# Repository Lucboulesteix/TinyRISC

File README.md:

# TinyRISC
 TINYRISC is a project to design and build an 8-bit computer using discrete logic components
 See "descriptive document.docx" for technical information

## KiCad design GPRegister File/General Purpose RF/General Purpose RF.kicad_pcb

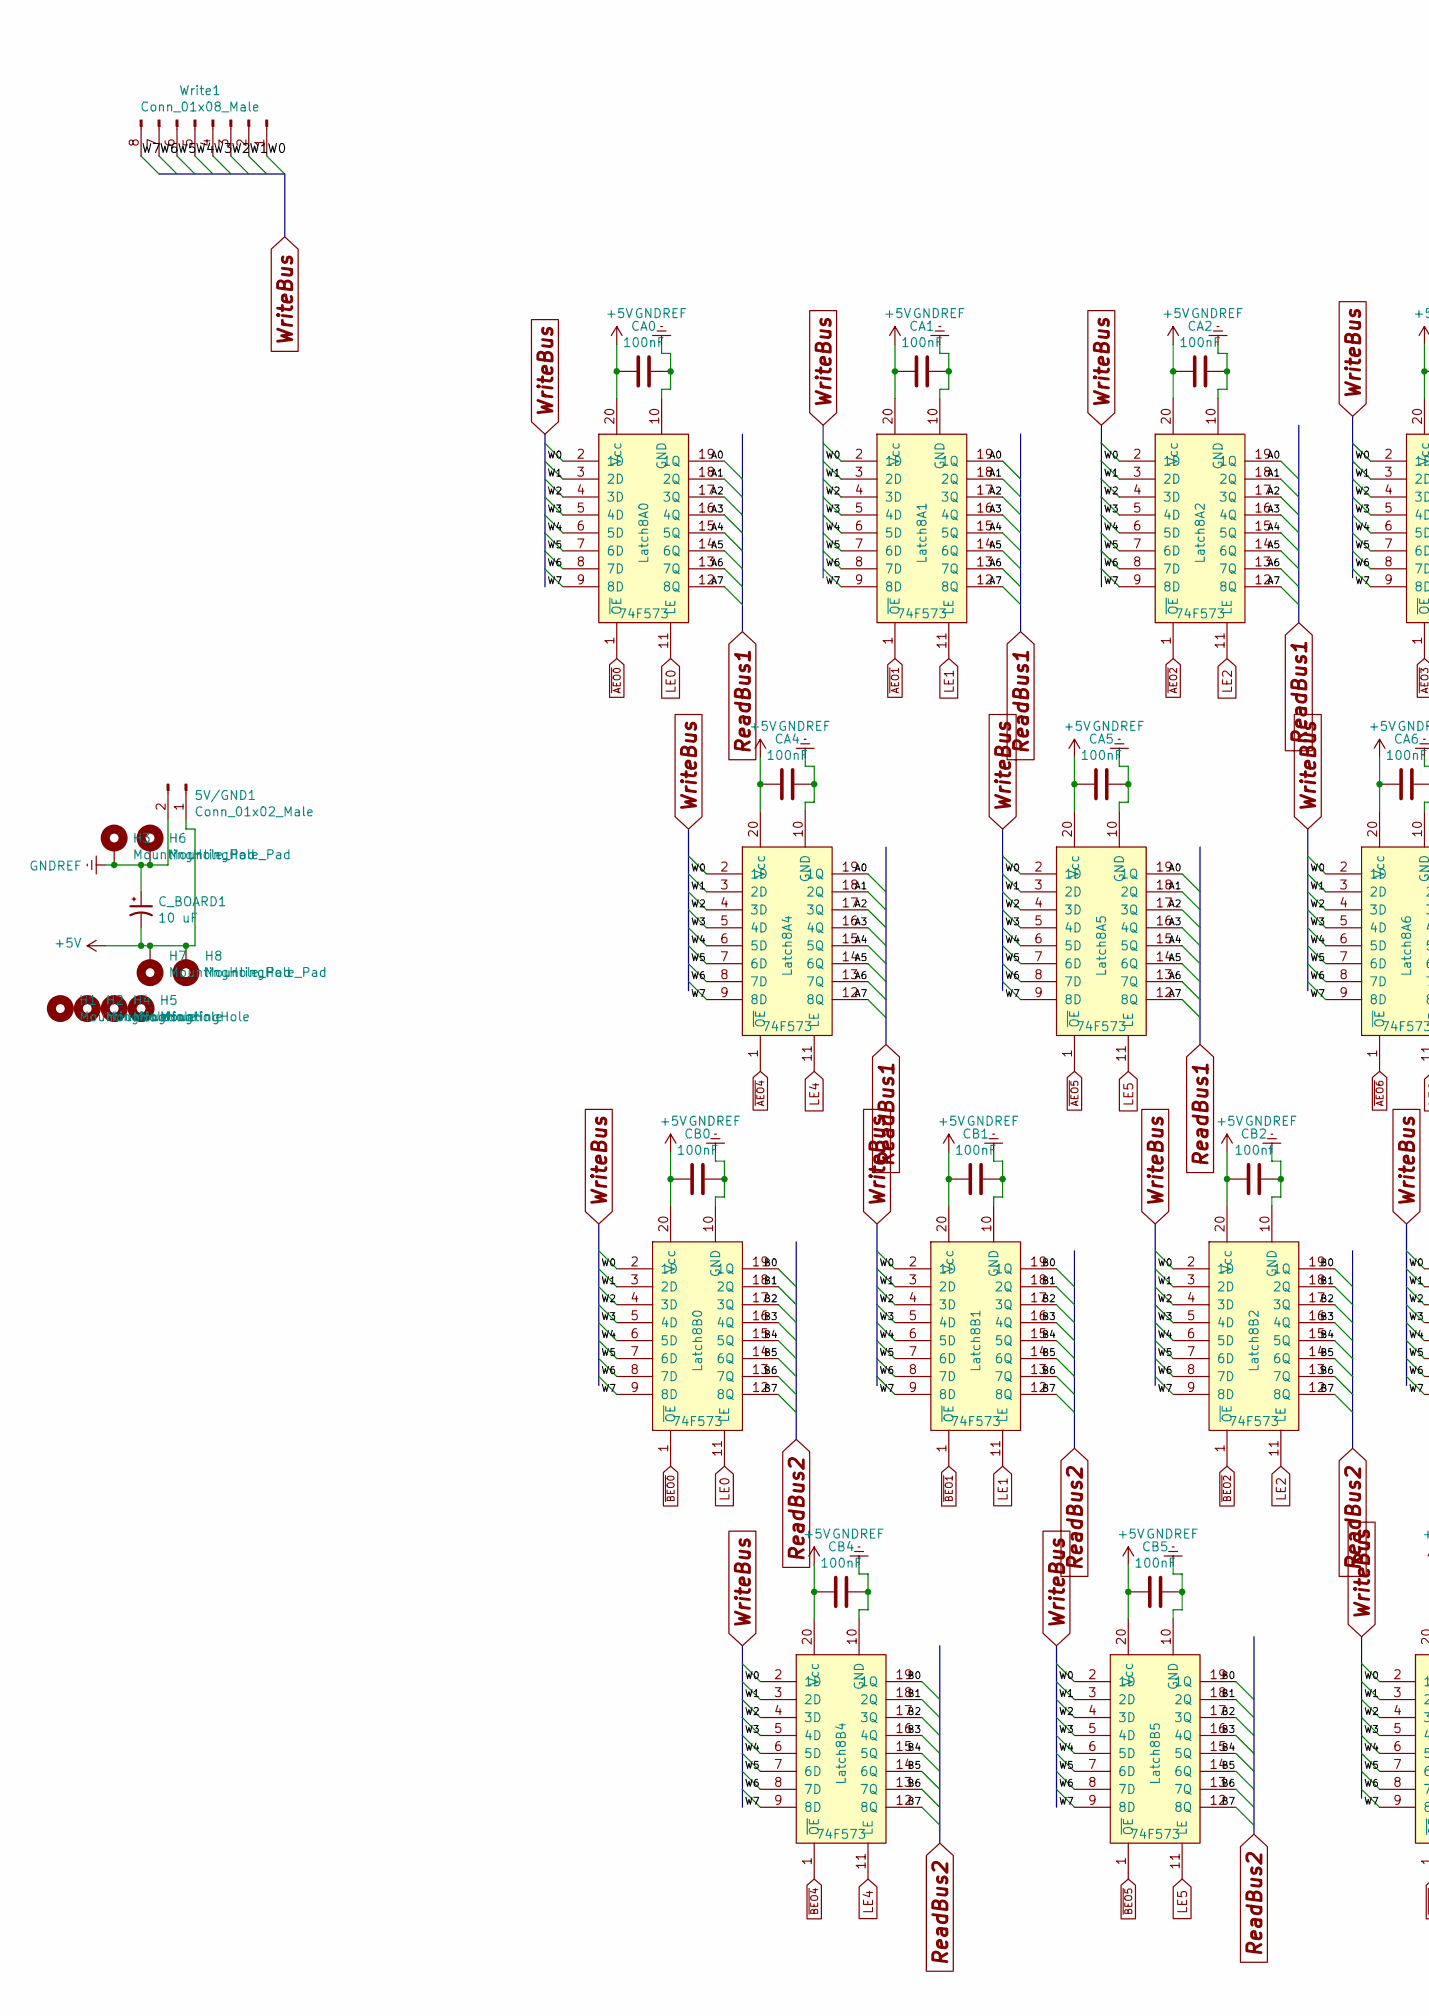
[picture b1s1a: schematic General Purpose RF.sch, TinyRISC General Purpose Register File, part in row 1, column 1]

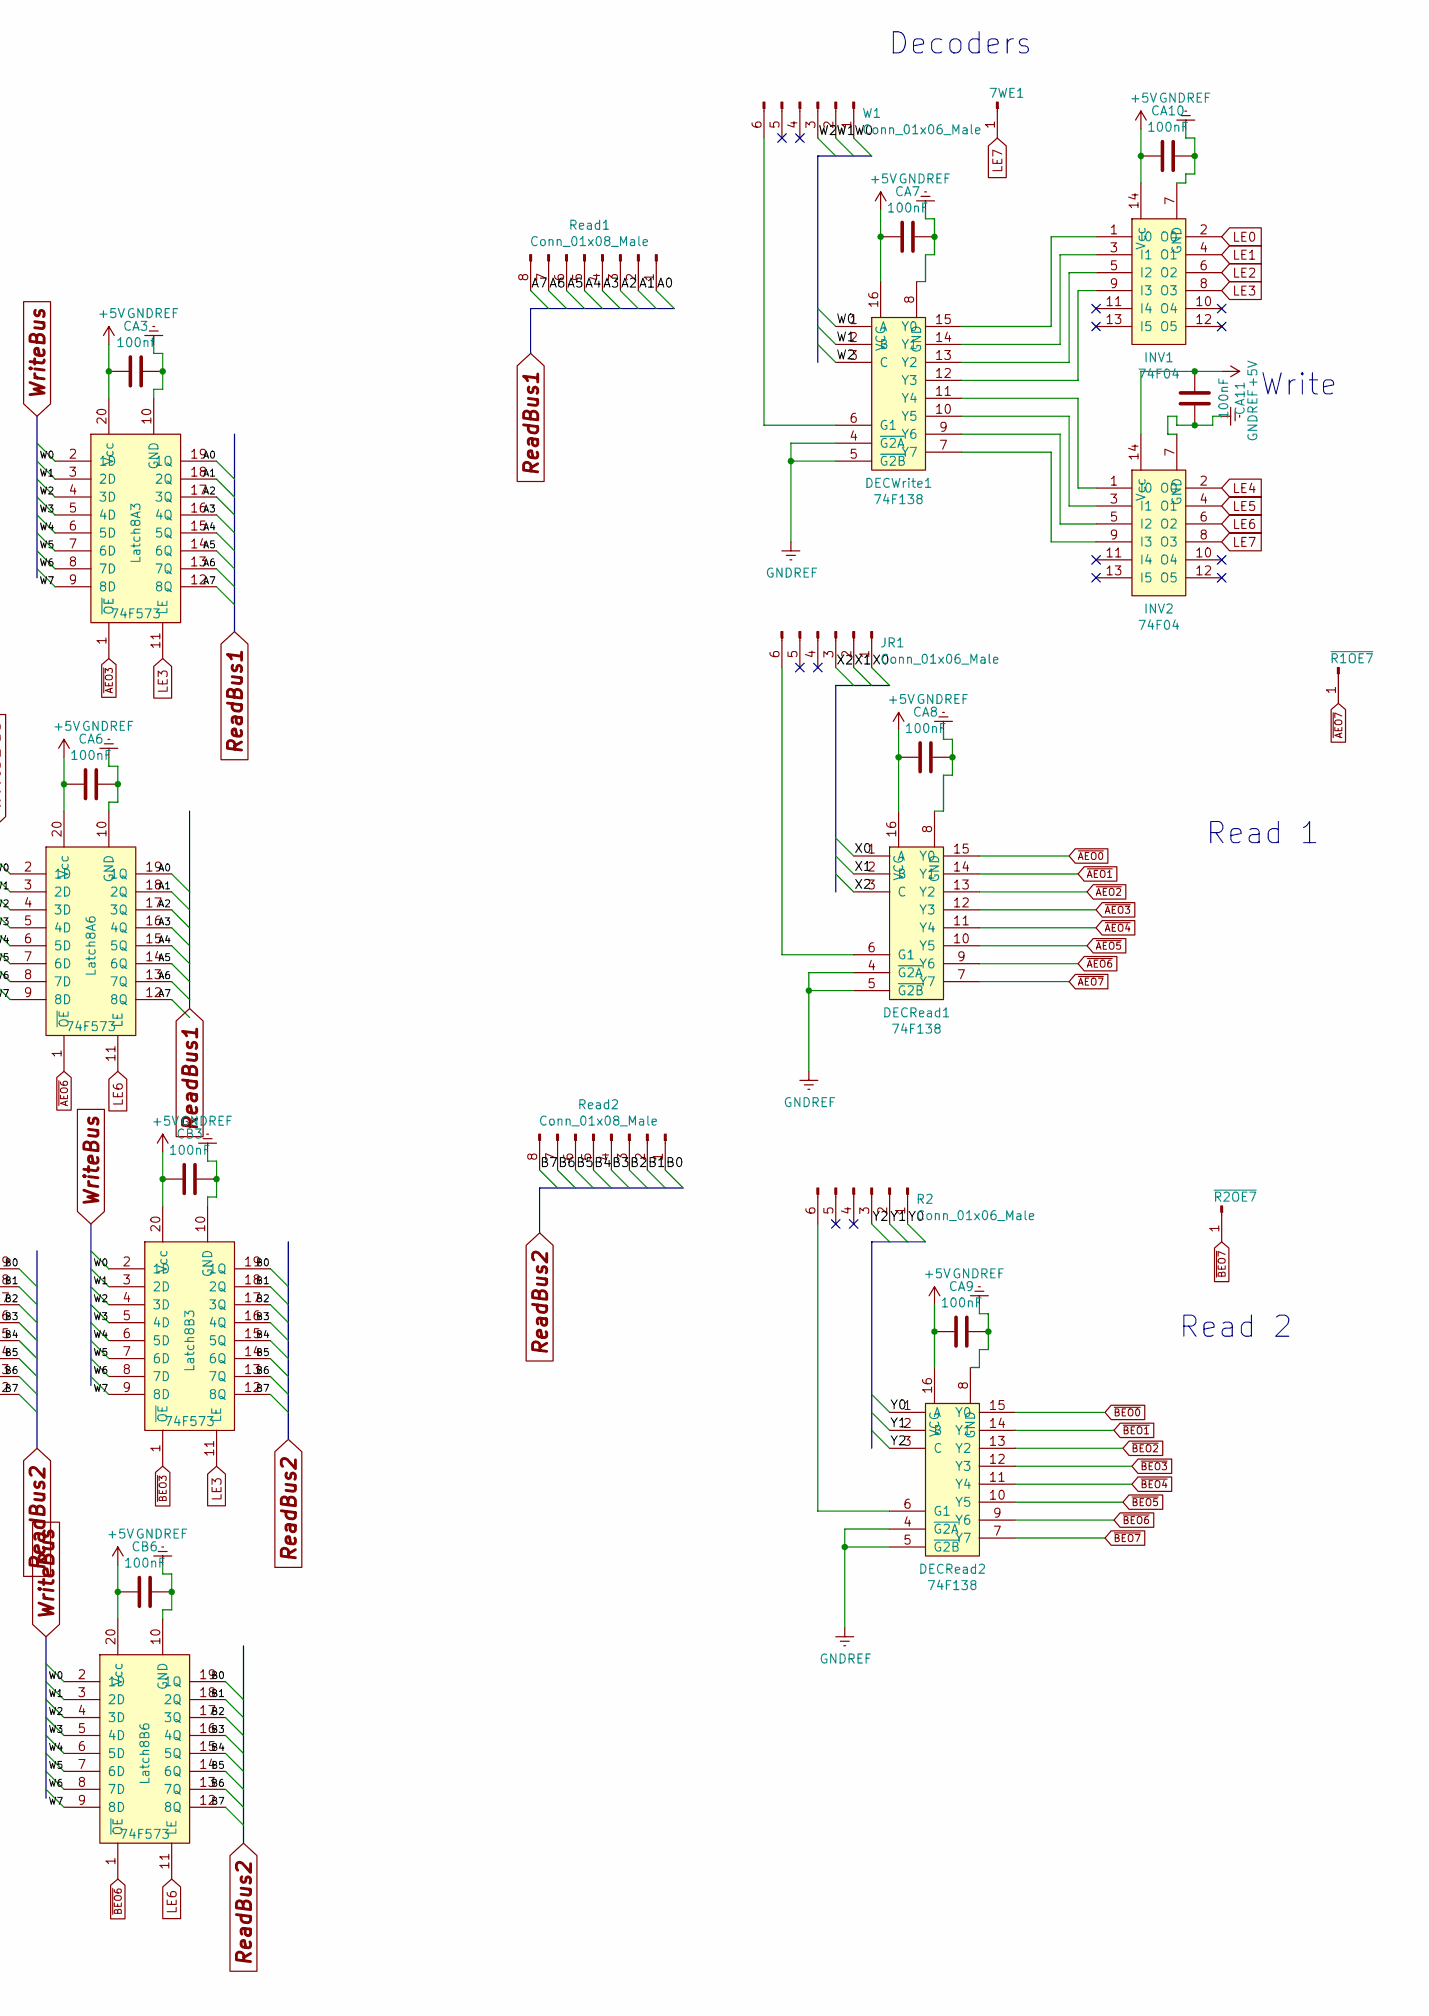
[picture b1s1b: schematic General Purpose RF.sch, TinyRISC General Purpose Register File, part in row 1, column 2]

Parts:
5V/GND1: Conn_01x02_Male; JST_XH_B2B-XH-AM_1x02_P2.50mm_Vertical
7WE1: Conn_01x01_Male; Pin_D1.0mm_L10.0mm
CA0, CA1, CA2, CA4, CA5, CA6, CA7, CA8, CA9, CA10, CA11: 100nF; C_Axial_L5.1mm_D3.1mm_P7.50mm_Horizontal
CA3: 100nf; C_Axial_L5.1mm_D3.1mm_P7.50mm_Horizontal
CB0, CB1, CB3, CB4, CB5, CB6: 100nF; C_Axial_L5.1mm_D3.1mm_P7.50mm_Horizontal
CB2: 100nf; C_Axial_L5.1mm_D3.1mm_P7.50mm_Horizontal
C_BOARD1: 10 uF; CP_Radial_D10.0mm_P5.00mm
DECRead1, DECRead2: 74F138; DIP-20_W7.62mm
DECWrite1: 74F138; DIP-20_W7.62mm
H1, H2, H4, H5: MountingHole; MountingHole_3.5mm_Pad_Via
H3, H6, H7, H8: MountingHole_Pad; MountingHole_3.5mm_Pad_Via
INV1, INV2: 74F04; DIP-14_W7.62mm
JR1: Conn_01x06_Male; 6pinIDC
Latch8A0, Latch8A1, Latch8A2, Latch8A3, Latch8A4, Latch8A5, Latch8A6, Latch8B0, Latch8B1, Latch8B2, Latch8B3, Latch8B4, Latch8B5, Latch8B6: 74F573; DIP-20_W7.62mm
R2: Conn_01x06_Male; 6pinIDC
Read1, Read2: Conn_01x08_Male; 16pinIDC
W1: Conn_01x06_Male; 6pinIDC
Write1: Conn_01x08_Male; 16pinIDC
~R1OE7, ~R2OE7: Conn_01x01_Male; Pin_D1.0mm_L10.0mm

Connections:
+5V: 5V/GND1.1, CA0.1, CA1.1, CA2.1, CA3.1, CA4.1, CA5.1, CA6.1, CA7.1, CA8.1, CA9.1, CA10.1, CA11.1, CB0.1, CB1.1, CB2.1, CB3.1, CB4.1, CB5.1, CB6.1, C_BOARD1.2, DECRead1.16 (VCC), DECRead2.16 (VCC), DECWrite1.16 (VCC), H7.1, H8.1, INV1.14 (Vcc), INV2.14 (Vcc), Latch8A0.20 (Vcc), Latch8A1.20 (Vcc), Latch8A2.20 (Vcc), Latch8A3.20 (Vcc), Latch8A4.20 (Vcc), Latch8A5.20 (Vcc), Latch8A6.20 (Vcc), Latch8B0.20 (Vcc), Latch8B1.20 (Vcc), Latch8B2.20 (Vcc), Latch8B3.20 (Vcc), Latch8B4.20 (Vcc), Latch8B5.20 (Vcc), Latch8B6.20 (Vcc)
/A0: Latch8A0.19 (1Q), Latch8A1.19 (1Q), Latch8A2.19 (1Q), Latch8A3.19 (1Q), Latch8A4.19 (1Q), Latch8A5.19 (1Q), Latch8A6.19 (1Q), Read1.1
/A1: Latch8A0.18 (2Q), Latch8A1.18 (2Q), Latch8A2.18 (2Q), Latch8A3.18 (2Q), Latch8A4.18 (2Q), Latch8A5.18 (2Q), Latch8A6.18 (2Q), Read1.2
/A2: Latch8A0.17 (3Q), Latch8A1.17 (3Q), Latch8A2.17 (3Q), Latch8A3.17 (3Q), Latch8A4.17 (3Q), Latch8A5.17 (3Q), Latch8A6.17 (3Q), Read1.3
/A3: Latch8A0.16 (4Q), Latch8A1.16 (4Q), Latch8A2.16 (4Q), Latch8A3.16 (4Q), Latch8A4.16 (4Q), Latch8A5.16 (4Q), Latch8A6.16 (4Q), Read1.4
/A4: Latch8A0.15 (5Q), Latch8A1.15 (5Q), Latch8A2.15 (5Q), Latch8A3.15 (5Q), Latch8A4.15 (5Q), Latch8A5.15 (5Q), Latch8A6.15 (5Q), Read1.5
/A5: Latch8A0.14 (6Q), Latch8A1.14 (6Q), Latch8A2.14 (6Q), Latch8A3.14 (6Q), Latch8A4.14 (6Q), Latch8A5.14 (6Q), Latch8A6.14 (6Q), Read1.6
/A6: Latch8A0.13 (7Q), Latch8A1.13 (7Q), Latch8A2.13 (7Q), Latch8A3.13 (7Q), Latch8A4.13 (7Q), Latch8A5.13 (7Q), Latch8A6.13 (7Q), Read1.7
/A7: Latch8A0.12 (8Q), Latch8A1.12 (8Q), Latch8A2.12 (8Q), Latch8A3.12 (8Q), Latch8A4.12 (8Q), Latch8A5.12 (8Q), Latch8A6.12 (8Q), Read1.8
/B0: Latch8B0.19 (1Q), Latch8B1.19 (1Q), Latch8B2.19 (1Q), Latch8B3.19 (1Q), Latch8B4.19 (1Q), Latch8B5.19 (1Q), Latch8B6.19 (1Q), Read2.1
/B1: Latch8B0.18 (2Q), Latch8B1.18 (2Q), Latch8B2.18 (2Q), Latch8B3.18 (2Q), Latch8B4.18 (2Q), Latch8B5.18 (2Q), Latch8B6.18 (2Q), Read2.2
/B2: Latch8B0.17 (3Q), Latch8B1.17 (3Q), Latch8B2.17 (3Q), Latch8B3.17 (3Q), Latch8B4.17 (3Q), Latch8B5.17 (3Q), Latch8B6.17 (3Q), Read2.3
/B3: Latch8B0.16 (4Q), Latch8B1.16 (4Q), Latch8B2.16 (4Q), Latch8B3.16 (4Q), Latch8B4.16 (4Q), Latch8B5.16 (4Q), Latch8B6.16 (4Q), Read2.4
/B4: Latch8B0.15 (5Q), Latch8B1.15 (5Q), Latch8B2.15 (5Q), Latch8B3.15 (5Q), Latch8B4.15 (5Q), Latch8B5.15 (5Q), Latch8B6.15 (5Q), Read2.5
/B5: Latch8B0.14 (6Q), Latch8B1.14 (6Q), Latch8B2.14 (6Q), Latch8B3.14 (6Q), Latch8B4.14 (6Q), Latch8B5.14 (6Q), Latch8B6.14 (6Q), Read2.6
/B6: Latch8B0.13 (7Q), Latch8B1.13 (7Q), Latch8B2.13 (7Q), Latch8B3.13 (7Q), Latch8B4.13 (7Q), Latch8B5.13 (7Q), Latch8B6.13 (7Q), Read2.7
/B7: Latch8B0.12 (8Q), Latch8B1.12 (8Q), Latch8B2.12 (8Q), Latch8B3.12 (8Q), Latch8B4.12 (8Q), Latch8B5.12 (8Q), Latch8B6.12 (8Q), Read2.8
/W0: DECWrite1.1 (A), Latch8A0.2 (1D), Latch8A1.2 (1D), Latch8A2.2 (1D), Latch8A3.2 (1D), Latch8A4.2 (1D), Latch8A5.2 (1D), Latch8A6.2 (1D), Latch8B0.2 (1D), Latch8B1.2 (1D), Latch8B2.2 (1D), Latch8B3.2 (1D), Latch8B4.2 (1D), Latch8B5.2 (1D), Latch8B6.2 (1D), W1.1, Write1.1
/W1: DECWrite1.2 (B), Latch8A0.3 (2D), Latch8A1.3 (2D), Latch8A2.3 (2D), Latch8A3.3 (2D), Latch8A4.3 (2D), Latch8A5.3 (2D), Latch8A6.3 (2D), Latch8B0.3 (2D), Latch8B1.3 (2D), Latch8B2.3 (2D), Latch8B3.3 (2D), Latch8B4.3 (2D), Latch8B5.3 (2D), Latch8B6.3 (2D), W1.2, Write1.2
/W2: DECWrite1.3 (C), Latch8A0.4 (3D), Latch8A1.4 (3D), Latch8A2.4 (3D), Latch8A3.4 (3D), Latch8A4.4 (3D), Latch8A5.4 (3D), Latch8A6.4 (3D), Latch8B0.4 (3D), Latch8B1.4 (3D), Latch8B2.4 (3D), Latch8B3.4 (3D), Latch8B4.4 (3D), Latch8B5.4 (3D), Latch8B6.4 (3D), W1.3, Write1.3
/W3: Latch8A0.5 (4D), Latch8A1.5 (4D), Latch8A2.5 (4D), Latch8A3.5 (4D), Latch8A4.5 (4D), Latch8A5.5 (4D), Latch8A6.5 (4D), Latch8B0.5 (4D), Latch8B1.5 (4D), Latch8B2.5 (4D), Latch8B3.5 (4D), Latch8B4.5 (4D), Latch8B5.5 (4D), Latch8B6.5 (4D), Write1.4
/W4: Latch8A0.6 (5D), Latch8A1.6 (5D), Latch8A2.6 (5D), Latch8A3.6 (5D), Latch8A4.6 (5D), Latch8A5.6 (5D), Latch8A6.6 (5D), Latch8B0.6 (5D), Latch8B1.6 (5D), Latch8B2.6 (5D), Latch8B3.6 (5D), Latch8B4.6 (5D), Latch8B5.6 (5D), Latch8B6.6 (5D), Write1.5
/W5: Latch8A0.7 (6D), Latch8A1.7 (6D), Latch8A2.7 (6D), Latch8A3.7 (6D), Latch8A4.7 (6D), Latch8A5.7 (6D), Latch8A6.7 (6D), Latch8B0.7 (6D), Latch8B1.7 (6D), Latch8B2.7 (6D), Latch8B3.7 (6D), Latch8B4.7 (6D), Latch8B5.7 (6D), Latch8B6.7 (6D), Write1.6
/W6: Latch8A0.8 (7D), Latch8A1.8 (7D), Latch8A2.8 (7D), Latch8A3.8 (7D), Latch8A4.8 (7D), Latch8A5.8 (7D), Latch8A6.8 (7D), Latch8B0.8 (7D), Latch8B1.8 (7D), Latch8B2.8 (7D), Latch8B3.8 (7D), Latch8B4.8 (7D), Latch8B5.8 (7D), Latch8B6.8 (7D), Write1.7
/W7: Latch8A0.9 (8D), Latch8A1.9 (8D), Latch8A2.9 (8D), Latch8A3.9 (8D), Latch8A4.9 (8D), Latch8A5.9 (8D), Latch8A6.9 (8D), Latch8B0.9 (8D), Latch8B1.9 (8D), Latch8B2.9 (8D), Latch8B3.9 (8D), Latch8B4.9 (8D), Latch8B5.9 (8D), Latch8B6.9 (8D), Write1.8
/X0: DECRead1.1 (A), JR1.1; also elsewhere on the board
/X1: DECRead1.2 (B), JR1.2; also elsewhere on the board
/X2: DECRead1.3 (C), JR1.3; also elsewhere on the board
/Y0: DECRead2.1 (A), R2.1; also elsewhere on the board
/Y1: DECRead2.2 (B), R2.2; also elsewhere on the board
/Y2: DECRead2.3 (C), R2.3; also elsewhere on the board
GNDREF: 5V/GND1.2, CA0.2, CA1.2, CA2.2, CA3.2, CA4.2, CA5.2, CA6.2, CA7.2, CA8.2, CA9.2, CA10.2, CA11.2, CB0.2, CB1.2, CB2.2, CB3.2, CB4.2, CB5.2, CB6.2, C_BOARD1.1, DECRead1.4 (~G2A), DECRead1.5 (~G2B), DECRead1.8 (GND), DECRead2.4 (~G2A), DECRead2.5 (~G2B), DECRead2.8 (GND), DECWrite1.4 (~G2A), DECWrite1.5 (~G2B), DECWrite1.8 (GND), H3.1, H6.1, INV1.7 (GND), INV2.7 (GND), Latch8A0.10 (GND), Latch8A1.10 (GND), Latch8A2.10 (GND), Latch8A3.10 (GND), Latch8A4.10 (GND), Latch8A5.10 (GND), Latch8A6.10 (GND), Latch8B0.10 (GND), Latch8B1.10 (GND), Latch8B2.10 (GND), Latch8B3.10 (GND), Latch8B4.10 (GND), Latch8B5.10 (GND), Latch8B6.10 (GND)
LE0: INV1.2 (O0), Latch8A0.11 (LE), Latch8B0.11 (LE)
LE1: INV1.4 (O1), Latch8A1.11 (LE), Latch8B1.11 (LE)
LE2: INV1.6 (O2), Latch8A2.11 (LE), Latch8B2.11 (LE)
LE3: INV1.8 (O3), Latch8A3.11 (LE), Latch8B3.11 (LE)
LE4: INV2.2 (O0), Latch8A4.11 (LE), Latch8B4.11 (LE)
LE5: INV2.4 (O1), Latch8A5.11 (LE), Latch8B5.11 (LE)
LE6: INV2.6 (O2), Latch8A6.11 (LE), Latch8B6.11 (LE)
LE7: 7WE1.1, INV2.8 (O3)
unnamed 40: DECRead1.6 (G1), JR1.6; also elsewhere on the board
unnamed 41: DECRead2.6 (G1), R2.6; also elsewhere on the board
unnamed: DECWrite1.6 (G1), W1.6
unnamed: DECWrite1.7 (Y7), INV2.9 (I3)
unnamed: DECWrite1.9 (Y6), INV2.5 (I2)
unnamed: DECWrite1.10 (Y5), INV2.3 (I1)
unnamed: DECWrite1.11 (Y4), INV2.1 (I0)
unnamed: DECWrite1.12 (Y3), INV1.9 (I3)
unnamed: DECWrite1.13 (Y2), INV1.5 (I2)
unnamed: DECWrite1.14 (Y1), INV1.3 (I1)
unnamed: DECWrite1.15 (Y0), INV1.1 (I0)
~AEO0: DECRead1.15 (Y0), Latch8A0.1 (~OE)
~AEO1: DECRead1.14 (Y1), Latch8A1.1 (~OE)
~AEO2: DECRead1.13 (Y2), Latch8A2.1 (~OE)
~AEO3: DECRead1.12 (Y3), Latch8A3.1 (~OE)
~AEO4: DECRead1.11 (Y4), Latch8A4.1 (~OE)
~AEO5: DECRead1.10 (Y5), Latch8A5.1 (~OE)
~AEO6: DECRead1.9 (Y6), Latch8A6.1 (~OE)
~AEO7: DECRead1.7 (Y7), ~R1OE7.1
~BEO0: DECRead2.15 (Y0), Latch8B0.1 (~OE)
~BEO1: DECRead2.14 (Y1), Latch8B1.1 (~OE)
~BEO2: DECRead2.13 (Y2), Latch8B2.1 (~OE)
~BEO3: DECRead2.12 (Y3), Latch8B3.1 (~OE)
~BEO4: DECRead2.11 (Y4), Latch8B4.1 (~OE)
~BEO5: DECRead2.10 (Y5), Latch8B5.1 (~OE)
~BEO6: DECRead2.9 (Y6), Latch8B6.1 (~OE)
~BEO7: DECRead2.7 (Y7), ~R2OE7.1

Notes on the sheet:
Decoders
Write
Read 1
Read 2

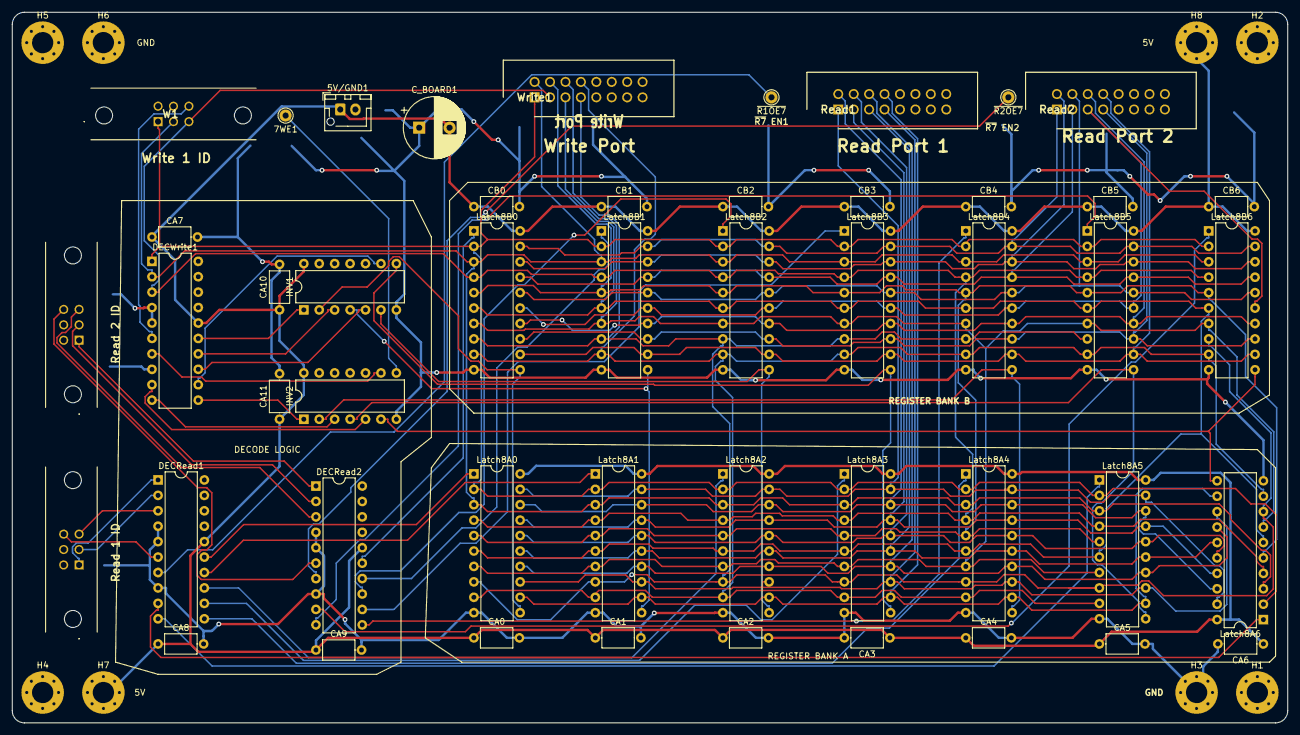
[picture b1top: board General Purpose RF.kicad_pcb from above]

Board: 2 copper layers, 210.0 x 117.0 mm, 55 parts (0 on the bottom side), 65 nets.

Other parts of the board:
Read 1 ID, Read 2 ID: Conn_01x06_Male; 6pinIDC

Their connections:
/X0: Read 1 ID.1; also elsewhere on the board
/X1: Read 1 ID.2; also elsewhere on the board
/X2: Read 1 ID.3; also elsewhere on the board
/Y0: Read 2 ID.1; also elsewhere on the board
/Y1: Read 2 ID.2; also elsewhere on the board
/Y2: Read 2 ID.3; also elsewhere on the board
unnamed 40: Read 1 ID.6; also elsewhere on the board
unnamed 41: Read 2 ID.6; also elsewhere on the board
